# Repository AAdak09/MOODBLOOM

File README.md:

# MOODBLOOM
🌸 Mood Bloom — Fidget Flower Keychain
Mood Bloom is a flower-shaped wearable PCB designed as a calming, interactive fidget keychain for emotional expression and anxiety relief. Each petal features an LED that lights up when its corresponding switch is pressed, representing different moods. When the device detects fidgeting (via a light sensor), the LEDs begin to flicker, and a vibration motor provides gentle haptic feedback — creating a soothing, sensory interaction.
# BOM
1. Red 5mm LED	
2.	6mm Tactile Push Button	SW1
3.	Photoresistor (LDR)	U1	1
4. Mini Vibration Motor (3V)	
5.	CR2032 Coin Cell Holder	
6. CR2032 Battery	
7.	220Ω Resistor	R1–R5
8.	10kΩ Resistor	R6
# 3D View

# Schematic 

# PCB

SLACK USERNAME: @Asmita Adak

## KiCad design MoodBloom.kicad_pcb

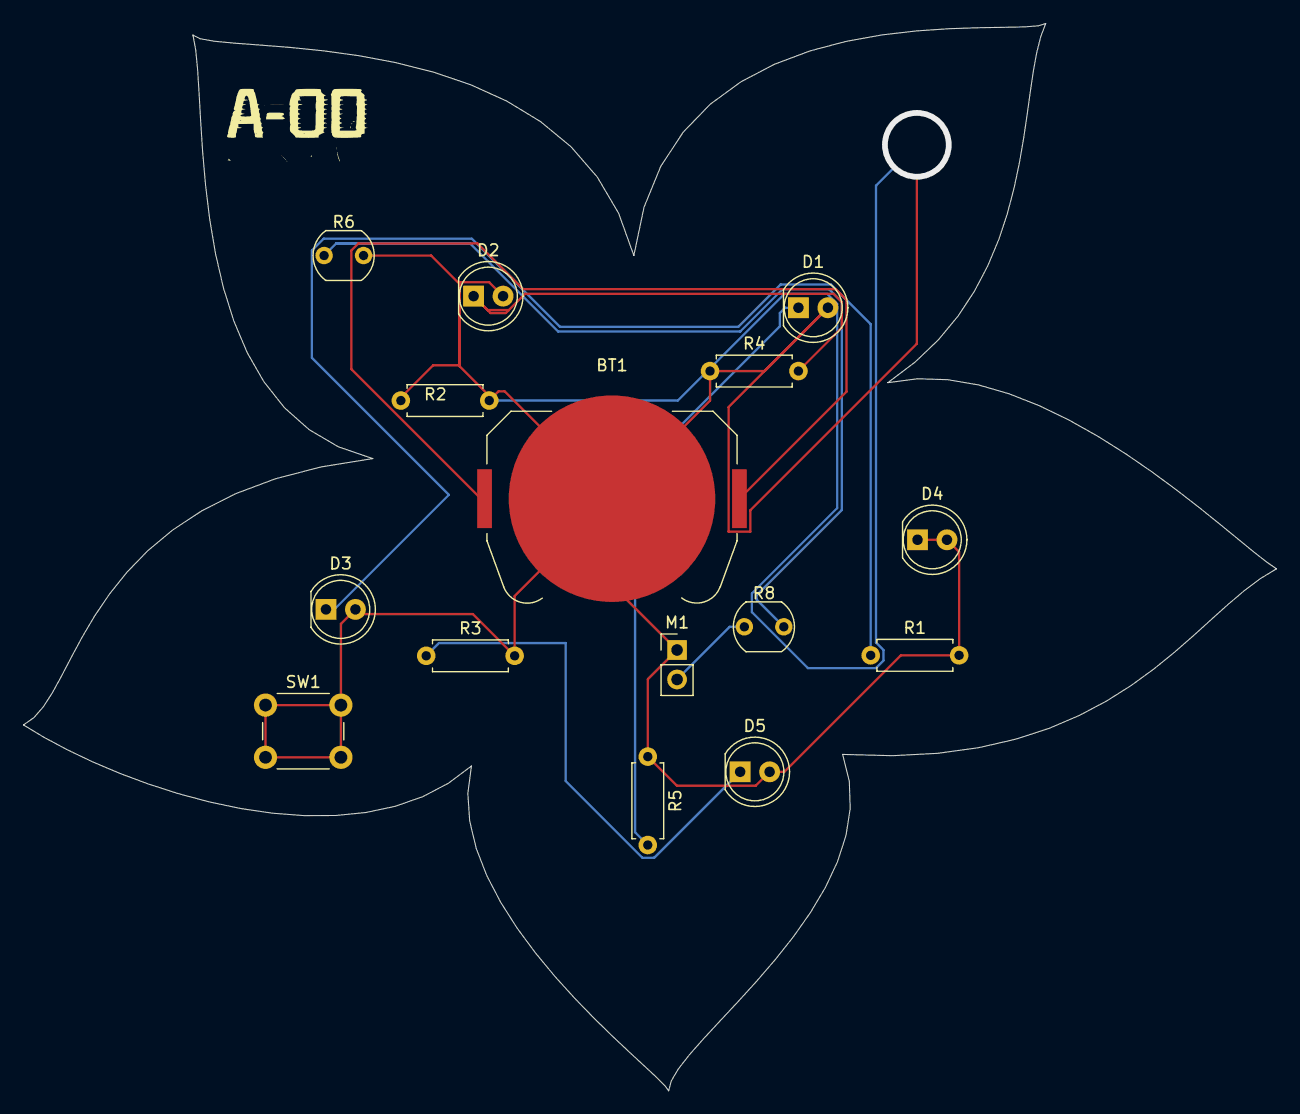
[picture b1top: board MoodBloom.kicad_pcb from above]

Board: 2 copper layers, 108.0 x 92.0 mm, 15 parts (0 on the bottom side), 7 nets.

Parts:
BT1: Battery; BatteryHolder_Keystone_3034_1x20mm
D1, D2, D3, D4, D5: LED; LED_D5.0mm
M1: Motor_DC; PinHeader_1x02_P2.54mm_Vertical
R1, R2, R3, R4, R5: R; R_Axial_DIN0207_L6.3mm_D2.5mm_P7.62mm_Horizontal
R6: R_Photo; R_LDR_5.1x4.3mm_P3.4mm_Vertical
R8: R; R_LDR_5.1x4.3mm_P3.4mm_Vertical
SW1: SW_Push; SW_PUSH_6mm

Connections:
GND: BT1.2 (-), D1.2 (A), D2.2 (A), D3.2 (A), D4.1 (K), D4.2 (A), D5.2 (A), M1.1 (+), R1.2, R2.1, R2.2, R3.2, R4.1, R5.1, R6.2, SW1.1, SW1.2
unnamed: D1.1 (K), R5.2
unnamed: D2.1 (K), R4.2
unnamed: D3.1 (K), R1.1
unnamed: D5.1 (K), R3.1
unnamed: M1.2 (-), R8.1
unnamed: R6.1, R8.2

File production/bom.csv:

Designator,Footprint,Quantity,Value,LCSC Part #
BT1,BatteryHolder_Keystone_3034_1x20mm,1,Battery,
"D1, D2, D3, D4, D5",LED_D5.0mm,5,LED,
M1,PinHeader_1x02_P2.54mm_Vertical,1,Motor_DC,
"R1, R2, R3, R4, R5",R_Axial_DIN0207_L6.3mm_D2.5mm_P7.62mm_Horizontal,5,R,
R6,R_LDR_5.1x4.3mm_P3.4mm_Vertical,1,R_Photo,
R8,R_LDR_5.1x4.3mm_P3.4mm_Vertical,1,R,
SW1,SW_PUSH_6mm,1,SW_Push,
